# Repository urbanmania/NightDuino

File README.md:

NightDuino
==========

Night light and white noise generator for my kids bedroom.

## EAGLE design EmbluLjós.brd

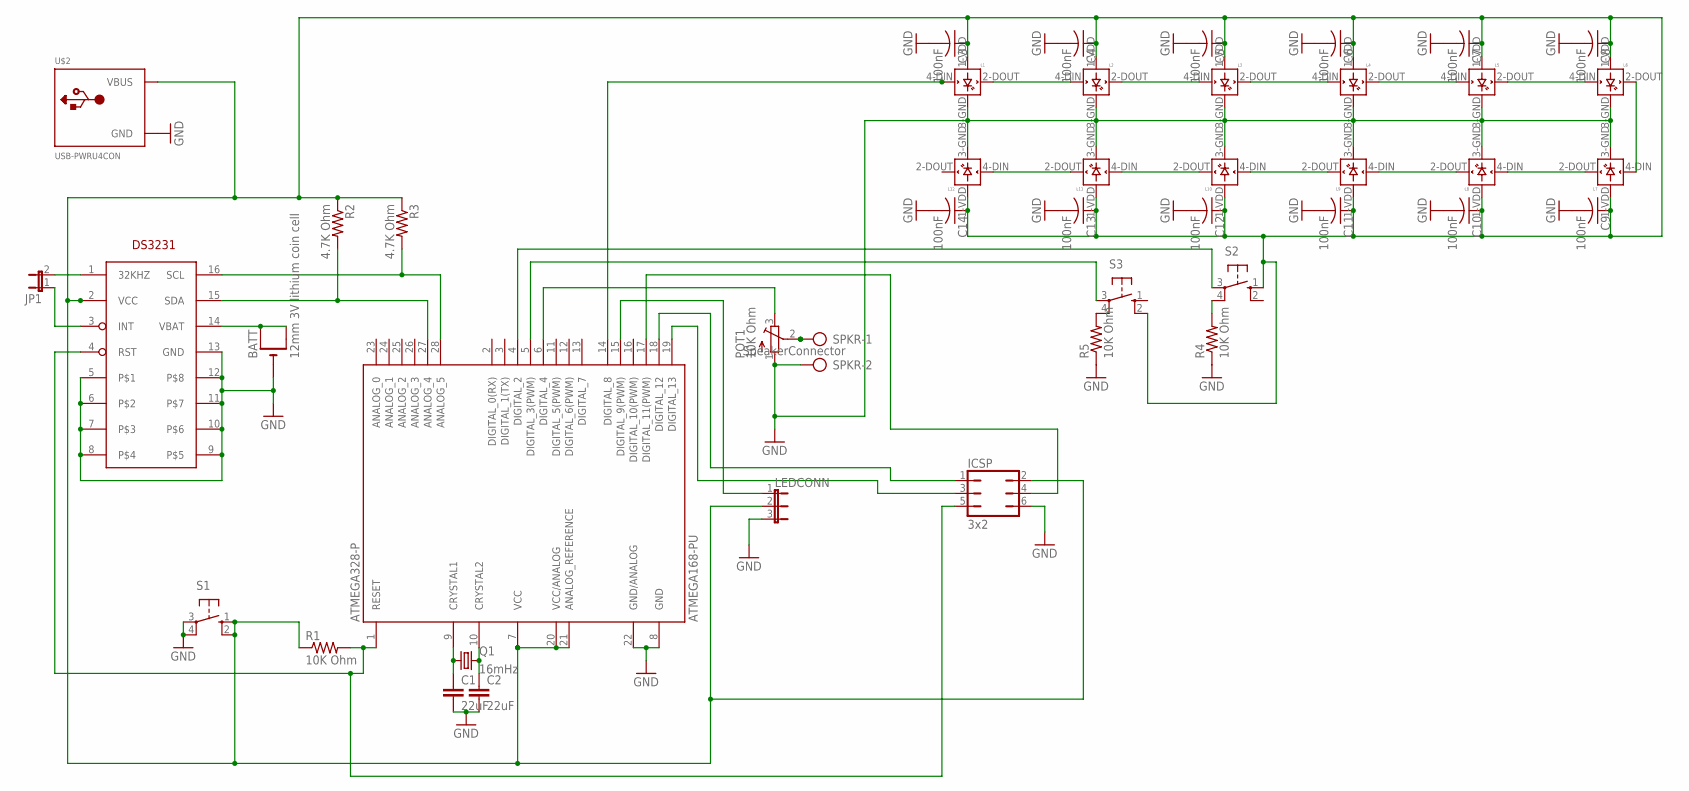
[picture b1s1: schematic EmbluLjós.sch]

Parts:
ATMEGA328-P: ATMEGA168-PU; DIL28-3
BATT: 12mm 3V lithium coin cell; CR1220-THM
C1, C2: 22uF; C0805
C3, C4, C5, C6, C7, C8, C9, C10, C11, C12, C13, C14: 100nF; C0805
ICSP: 3x2; JP3Q
JP1: JP1E; JP1
L1, L2, L3, L4, L5, L6, L7, L8, L9, L10, L11, L12: WS2812B
LEDCONN: JP2E; JP2
POT1: 10K Ohm; TC33X
Q1: 16mHz; HC49/S
R1, R4, R5: 10K Ohm; R0805
R2, R3: 4.7K Ohm; R0805
S1, S2, S3: 10-XX; B3F-10XX
SPKR: SpeakerConnector; AK500/2-H
U$1: DS3231; SO16
U$2: USB-PWRU4CON; USB-MINIB-THM-PWRONLY

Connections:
GND: ATMEGA328-P.8 (GND), ATMEGA328-P.22 (GND/ANALOG), BATT.-, C1.2, C2.2, C3.2, C4.2, C5.2, C6.2, C7.2, C8.2, C9.2, C10.2, C11.2, C12.2, C13.2, C14.2, ICSP.6, L1.3-GND (GND), L2.3-GND (GND), L3.3-GND (GND), L4.3-GND (GND), L5.3-GND (GND), L6.3-GND (GND), L7.3-GND (GND), L8.3-GND (GND), L9.3-GND (GND), L10.3-GND (GND), L11.3-GND (GND), L12.3-GND (GND), LEDCONN.3, POT1.1 (A), R4.1, R5.1, S1.3, S1.4 (P1), SPKR.2, U$1.5, U$1.6, U$1.7, U$1.8, U$1.9, U$1.10, U$1.11, U$1.12, U$1.13 (GND), U$2.GND
unnamed: ATMEGA328-P.1 (RESET), ICSP.5, R1.2, U$1.4 (RST)
unnamed: ATMEGA328-P.18 (DIGITAL_12), ICSP.1
unnamed: BATT.+1 (+), BATT.+2 (+1), U$1.14 (VBAT)
unnamed: POT1.2 (S), SPKR.1
unnamed: ATMEGA328-P.6 (DIGITAL_4), POT1.3 (E)
unnamed: ATMEGA328-P.28 (ANALOG_5), R3.2, U$1.16 (SCL)
unnamed: ATMEGA328-P.27 (ANALOG_4), R2.2, U$1.15 (SDA)
unnamed: ATMEGA328-P.10 (CRYSTAL2), C2.1, Q1.2
unnamed: ATMEGA328-P.9 (CRYSTAL1), C1.1, Q1.1
unnamed: ATMEGA328-P.15 (DIGITAL_9(PWM)), LEDCONN.1
unnamed: JP1.2, U$1.1 (32KHZ)
unnamed: JP1.1, U$1.3 (INT)
unnamed: L1.2-DOUT (DOUT), L2.4-DIN (DIN)
unnamed: L2.2-DOUT (DOUT), L3.4-DIN (DIN)
unnamed: L3.2-DOUT (DOUT), L4.4-DIN (DIN)
unnamed: L4.2-DOUT (DOUT), L5.4-DIN (DIN)
unnamed: L5.2-DOUT (DOUT), L6.4-DIN (DIN)
unnamed: ATMEGA328-P.19 (DIGITAL_13), ICSP.3
unnamed: L6.2-DOUT (DOUT), L7.4-DIN (DIN)
unnamed: L7.2-DOUT (DOUT), L8.4-DIN (DIN)
unnamed: L8.2-DOUT (DOUT), L9.4-DIN (DIN)
unnamed: L10.2-DOUT (DOUT), L11.4-DIN (DIN)
unnamed: L11.2-DOUT (DOUT), L12.4-DIN (DIN)
unnamed: L9.2-DOUT (DOUT), L10.4-DIN (DIN)
unnamed: ATMEGA328-P.4 (DIGITAL_2), S2.3
unnamed: R4.2, S2.4 (P1)
unnamed: ATMEGA328-P.7 (VCC), ATMEGA328-P.20 (VCC/ANALOG), ATMEGA328-P.21 (ANALOG_REFERENCE), C3.1, C4.1, C5.1, C6.1, C7.1, C8.1, C9.1, C10.1, C11.1, C12.1, C13.1, C14.1, ICSP.2, L1.1-VDD (VDD), L2.1-VDD (VDD), L3.1-VDD (VDD), L4.1-VDD (VDD), L5.1-VDD (VDD), L6.1-VDD (VDD), L7.1-VDD (VDD), L8.1-VDD (VDD), L9.1-VDD (VDD), L10.1-VDD (VDD), L11.1-VDD (VDD), L12.1-VDD (VDD), LEDCONN.2, R1.1, R2.1, R3.1, S1.1 (S), S1.2 (S1), S2.1 (S), S3.2 (S1), U$1.2 (VCC), U$2.VBUS
unnamed: R5.2, S3.4 (P1)
unnamed: ATMEGA328-P.5 (DIGITAL_3(PWM)), S3.3
unnamed: ATMEGA328-P.14 (DIGITAL_8), L1.4-DIN (DIN)
unnamed: ATMEGA328-P.17 (DIGITAL_11(PWM)), ICSP.4

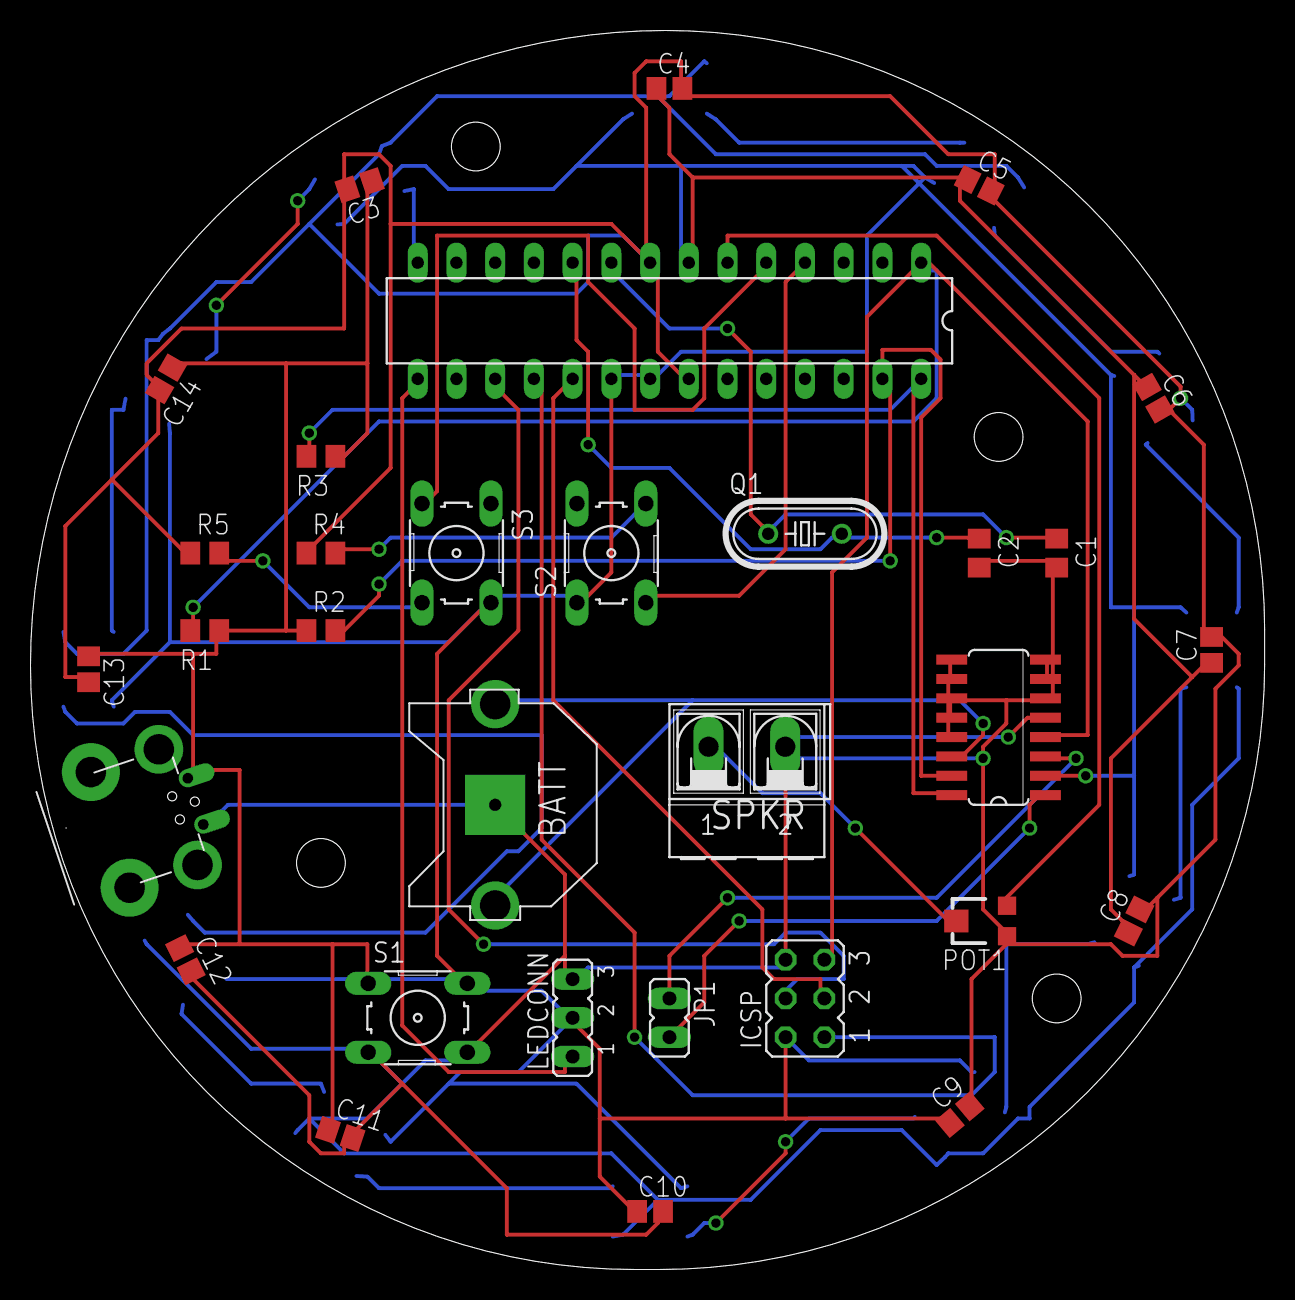
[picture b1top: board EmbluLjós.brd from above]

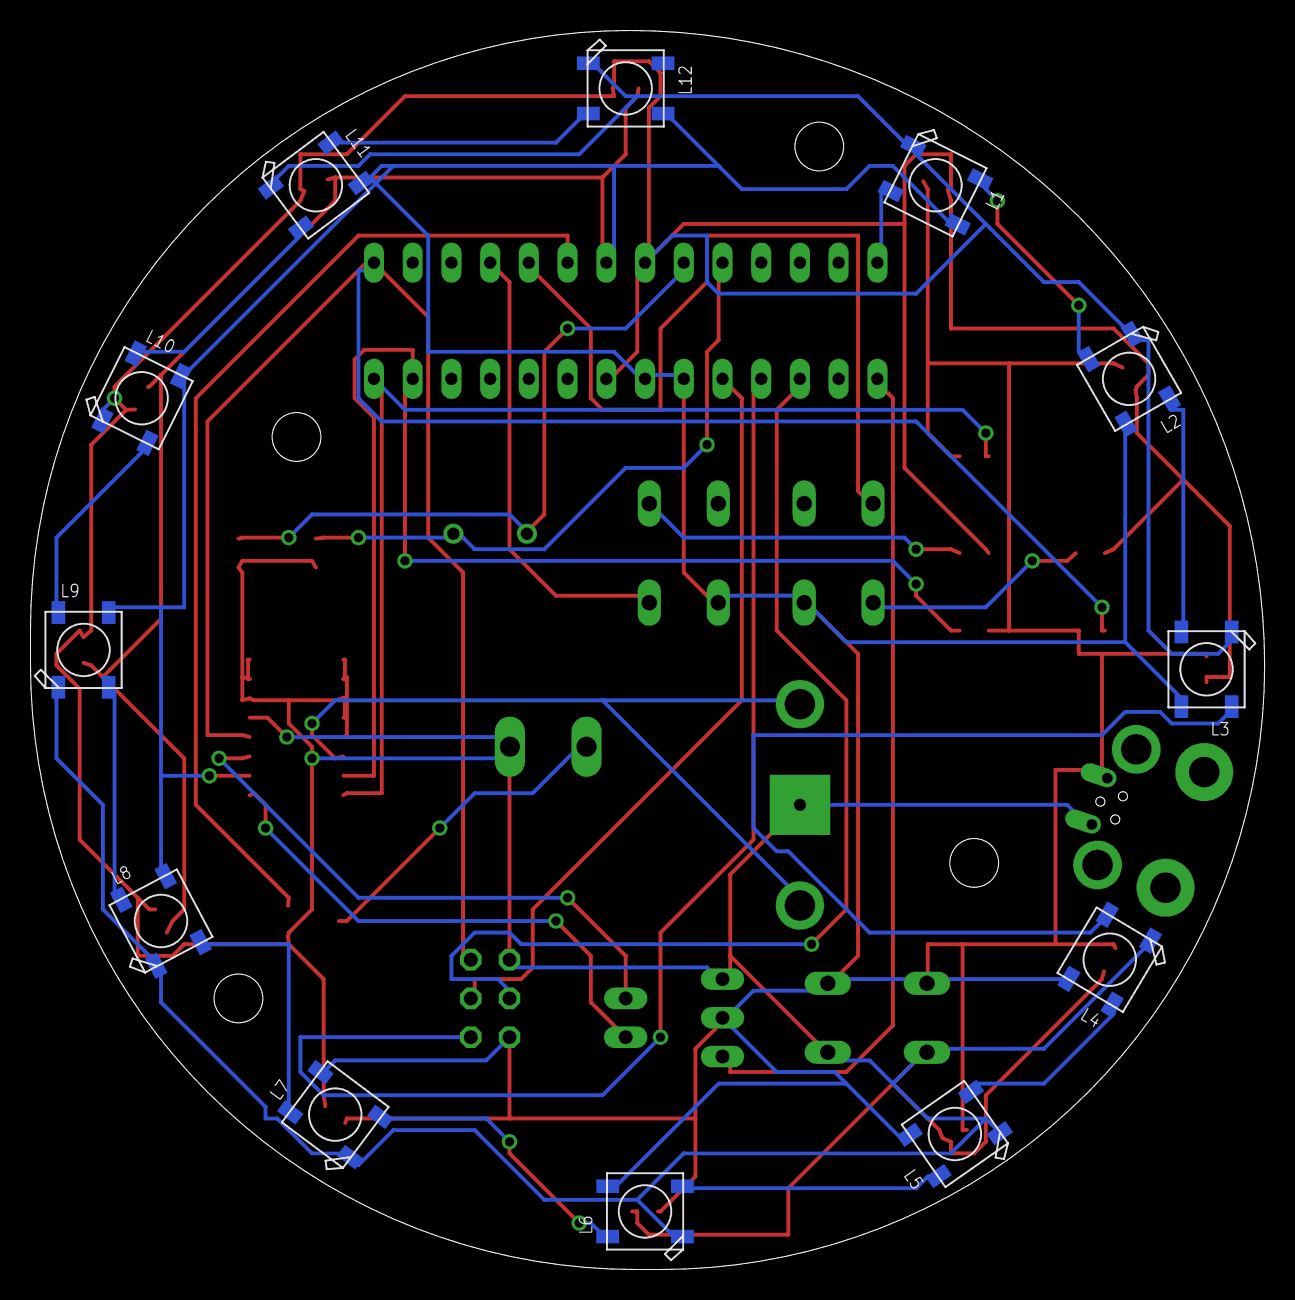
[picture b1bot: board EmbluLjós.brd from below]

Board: 2 copper layers, 81.0 x 81.3 mm, 44 parts (12 on the bottom side), 32 nets.

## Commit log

2014-03-27 Schematics and Board added
2014-06-10 Small fixes
    small fixes
